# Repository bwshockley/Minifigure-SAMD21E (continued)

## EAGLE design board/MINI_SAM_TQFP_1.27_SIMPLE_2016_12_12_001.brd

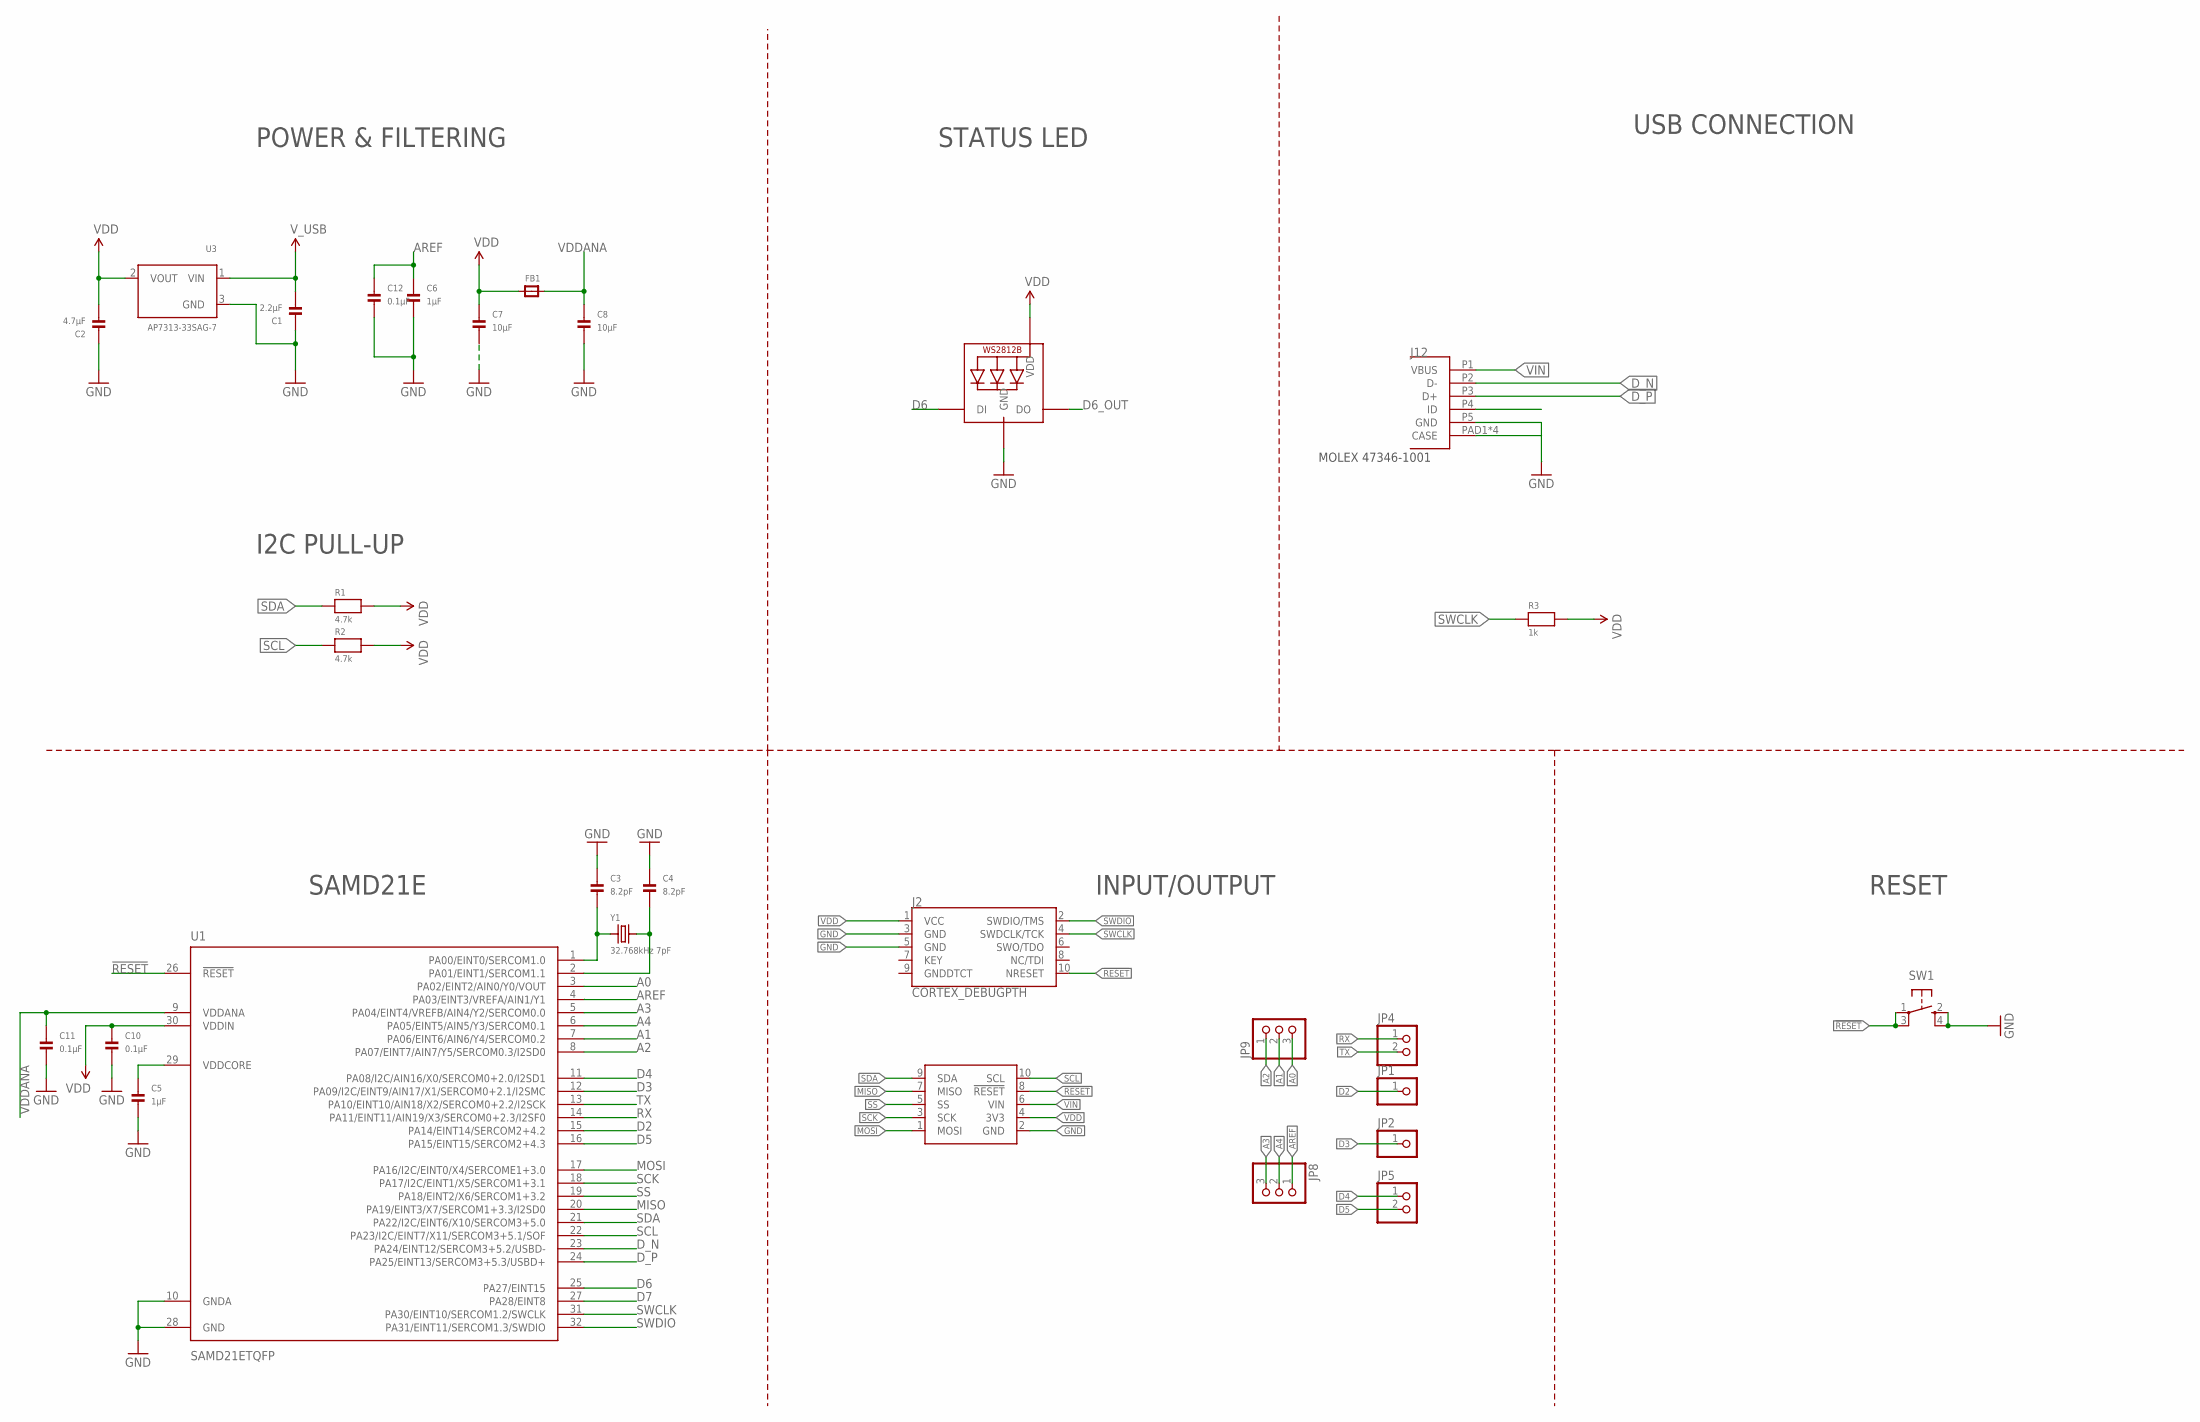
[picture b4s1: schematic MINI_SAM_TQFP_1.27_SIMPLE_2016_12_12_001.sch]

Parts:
C1: 2.2µF; _0805MP
C2: 4.7µF; _0805MP
C3, C4: 8.2pF; _0805MP
C5, C6: 1µF; _0805MP
C7, C8: 10µF; _0805MP
C10, C11, C12: 0.1µF; _0805MP
FB1: FERRITE_0805MP; _0805MP
J2: CORTEX_DEBUGPTH; 2X5-PTH-1.27MM
J12: MOLEX_47346-100147346; MOLEX_47346-1001
JP1, JP2: HEADER-1X1ROUND; 1X01_ROUND
JP4, JP5: HEADER-1X2ROUND; 1X02_ROUND
JP8, JP9: HEADER-1X3ROUND; 1X03_ROUND
R1, R2: 4.7k; _0805MP
R3: 1k; _0805MP
STATUS: WS2812B3535; LED3535
SW1: SPST_TACT-KMR2; KMR2
U1: SAMD21ETQFP; TQFP32-08
U3: AP7313-33SAG-7; SOT23-R
U$3: MINI_SAM_10_PIN; M50-360XXXX
Y1: 32.768kHz 7pF; _0805MP

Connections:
!RESET: J2.10 (NRESET), SW1.1, SW1.3 (P1), U1.26 (!RESET), U$3.8 (!RESET)
A0: JP9.3, U1.3 (PA02/EINT2/AIN0/Y0/VOUT)
A1: JP9.2, U1.7 (PA06/EINT6/AIN6/Y4/SERCOM0.2)
A2: JP9.1, U1.8 (PA07/EINT7/AIN7/Y5/SERCOM0.3/I2SD0)
A3: JP8.3, U1.5 (PA04/EINT4/VREFB/AIN4/Y2/SERCOM0.0)
A4: JP8.2, U1.6 (PA05/EINT5/AIN5/Y3/SERCOM0.1)
AREF: C6.1, C12.1, JP8.1, U1.4 (PA03/EINT3/VREFA/AIN1/Y1)
D2: JP1.1, U1.15 (PA14/EINT14/SERCOM2+4.2)
D3: JP2.1, U1.12 (PA09/I2C/EINT9/AIN17/X1/SERCOM0+2.1/I2S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)
D4: JP5.1, U1.11 (PA08/I2C/AIN16/X0/SERCOM0+2.0/I2SD1)
D5: JP5.2, U1.16 (PA15/EINT15/SERCOM2+4.3)
D6: STATUS.1 (DI), U1.25 (PA27/EINT15)
D6_OUT: STATUS.3 (DO)
D7: U1.27 (PA28/EINT8)
D_N: J12.P2 (D-), U1.23 (PA24/EINT12/SERCOM3+5.2/USBD-)
D_P: J12.P3 (D+), U1.24 (PA25/EINT13/SERCOM3+5.3/USBD+)
GND: C1.1, C2.1, C3.1, C4.1, C5.2, C6.2, C7.2, C8.2, C10.2, C11.2, C12.2, J2.3 (GND), J2.5 (GND), J12.P5 (GND), J12.PAD1 (CASE), J12.PAD2 (CASE), J12.PAD3 (CASE), J12.PAD4 (CASE), STATUS.4 (GND), SW1.2 (S), SW1.4 (S1), U1.10 (GNDA), U1.28 (GND), U3.3 (GND), U$3.2 (GND)
MISO: U1.20 (PA19/EINT3/X7/SERCOM1+3.3/I2SD0), U$3.7 (MISO)
MOSI: U1.17 (PA16/I2C/EINT0/X4/SERCOME1+3.0), U$3.1 (MOSI)
unnamed: C3.2, U1.1 (PA00/EINT0/SERCOM1.0), Y1.1
unnamed: C4.2, U1.2 (PA01/EINT1/SERCOM1.1), Y1.2
unnamed: C5.1, U1.29 (VDDCORE)
RX: JP4.1, U1.14 (PA11/EINT11/AIN19/X3/SERCOM0+2.3/I2SF0)
SCK: U1.18 (PA17/I2C/EINT1/X5/SERCOM1+3.1), U$3.3 (SCK)
SCL: R2.1, U1.22 (PA23/I2C/EINT7/X11/SERCOM3+5.1/SOF), U$3.10 (SCL)
SDA: R1.1, U1.21 (PA22/I2C/EINT6/X10/SERCOM3+5.0), U$3.9 (SDA)
SS: U1.19 (PA18/EINT2/X6/SERCOM1+3.2), U$3.5 (SS)
SWCLK: J2.4 (SWDCLK/TCK), R3.1, U1.31 (PA30/EINT10/SERCOM1.2/SWCLK)
SWDIO: J2.2 (SWDIO/TMS), U1.32 (PA31/EINT11/SERCOM1.3/SWDIO)
TX: JP4.2, U1.13 (PA10/EINT10/AIN18/X2/SERCOM0+2.2/I2SCK)
VDD: C2.2, C7.1, C10.1, FB1.1, J2.1 (VCC), R1.2, R2.2, R3.2, STATUS.2 (VDD), U1.30 (VDDIN), U3.2 (VOUT), U$3.4 (3V3)
VDDANA: C8.1, C11.1, FB1.2, U1.9 (VDDANA)
VIN: C1.2, J12.P1 (VBUS), U3.1 (VIN), U$3.6 (VIN)

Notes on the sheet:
INPUT/OUTPUT
RESET
POWER & FILTERING
SAMD21E
STATUS LED
USB CONNECTION
I2C PULL-UP
MOLEX 47346-1001

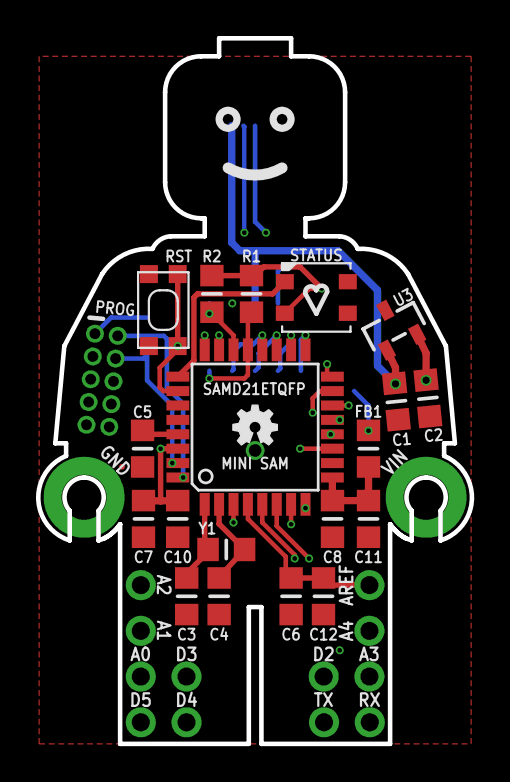
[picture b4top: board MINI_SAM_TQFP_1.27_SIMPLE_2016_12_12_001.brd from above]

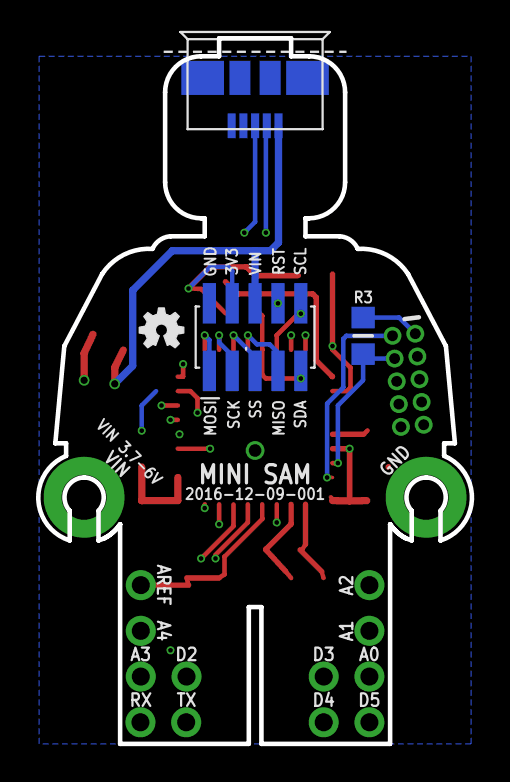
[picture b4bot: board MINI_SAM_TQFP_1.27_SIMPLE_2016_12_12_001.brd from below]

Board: 4 copper layers, 24.1 x 39.2 mm, 31 parts (4 on the bottom side), 31 nets.

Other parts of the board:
U$1, U$2: OSHW-LOGO-MINI

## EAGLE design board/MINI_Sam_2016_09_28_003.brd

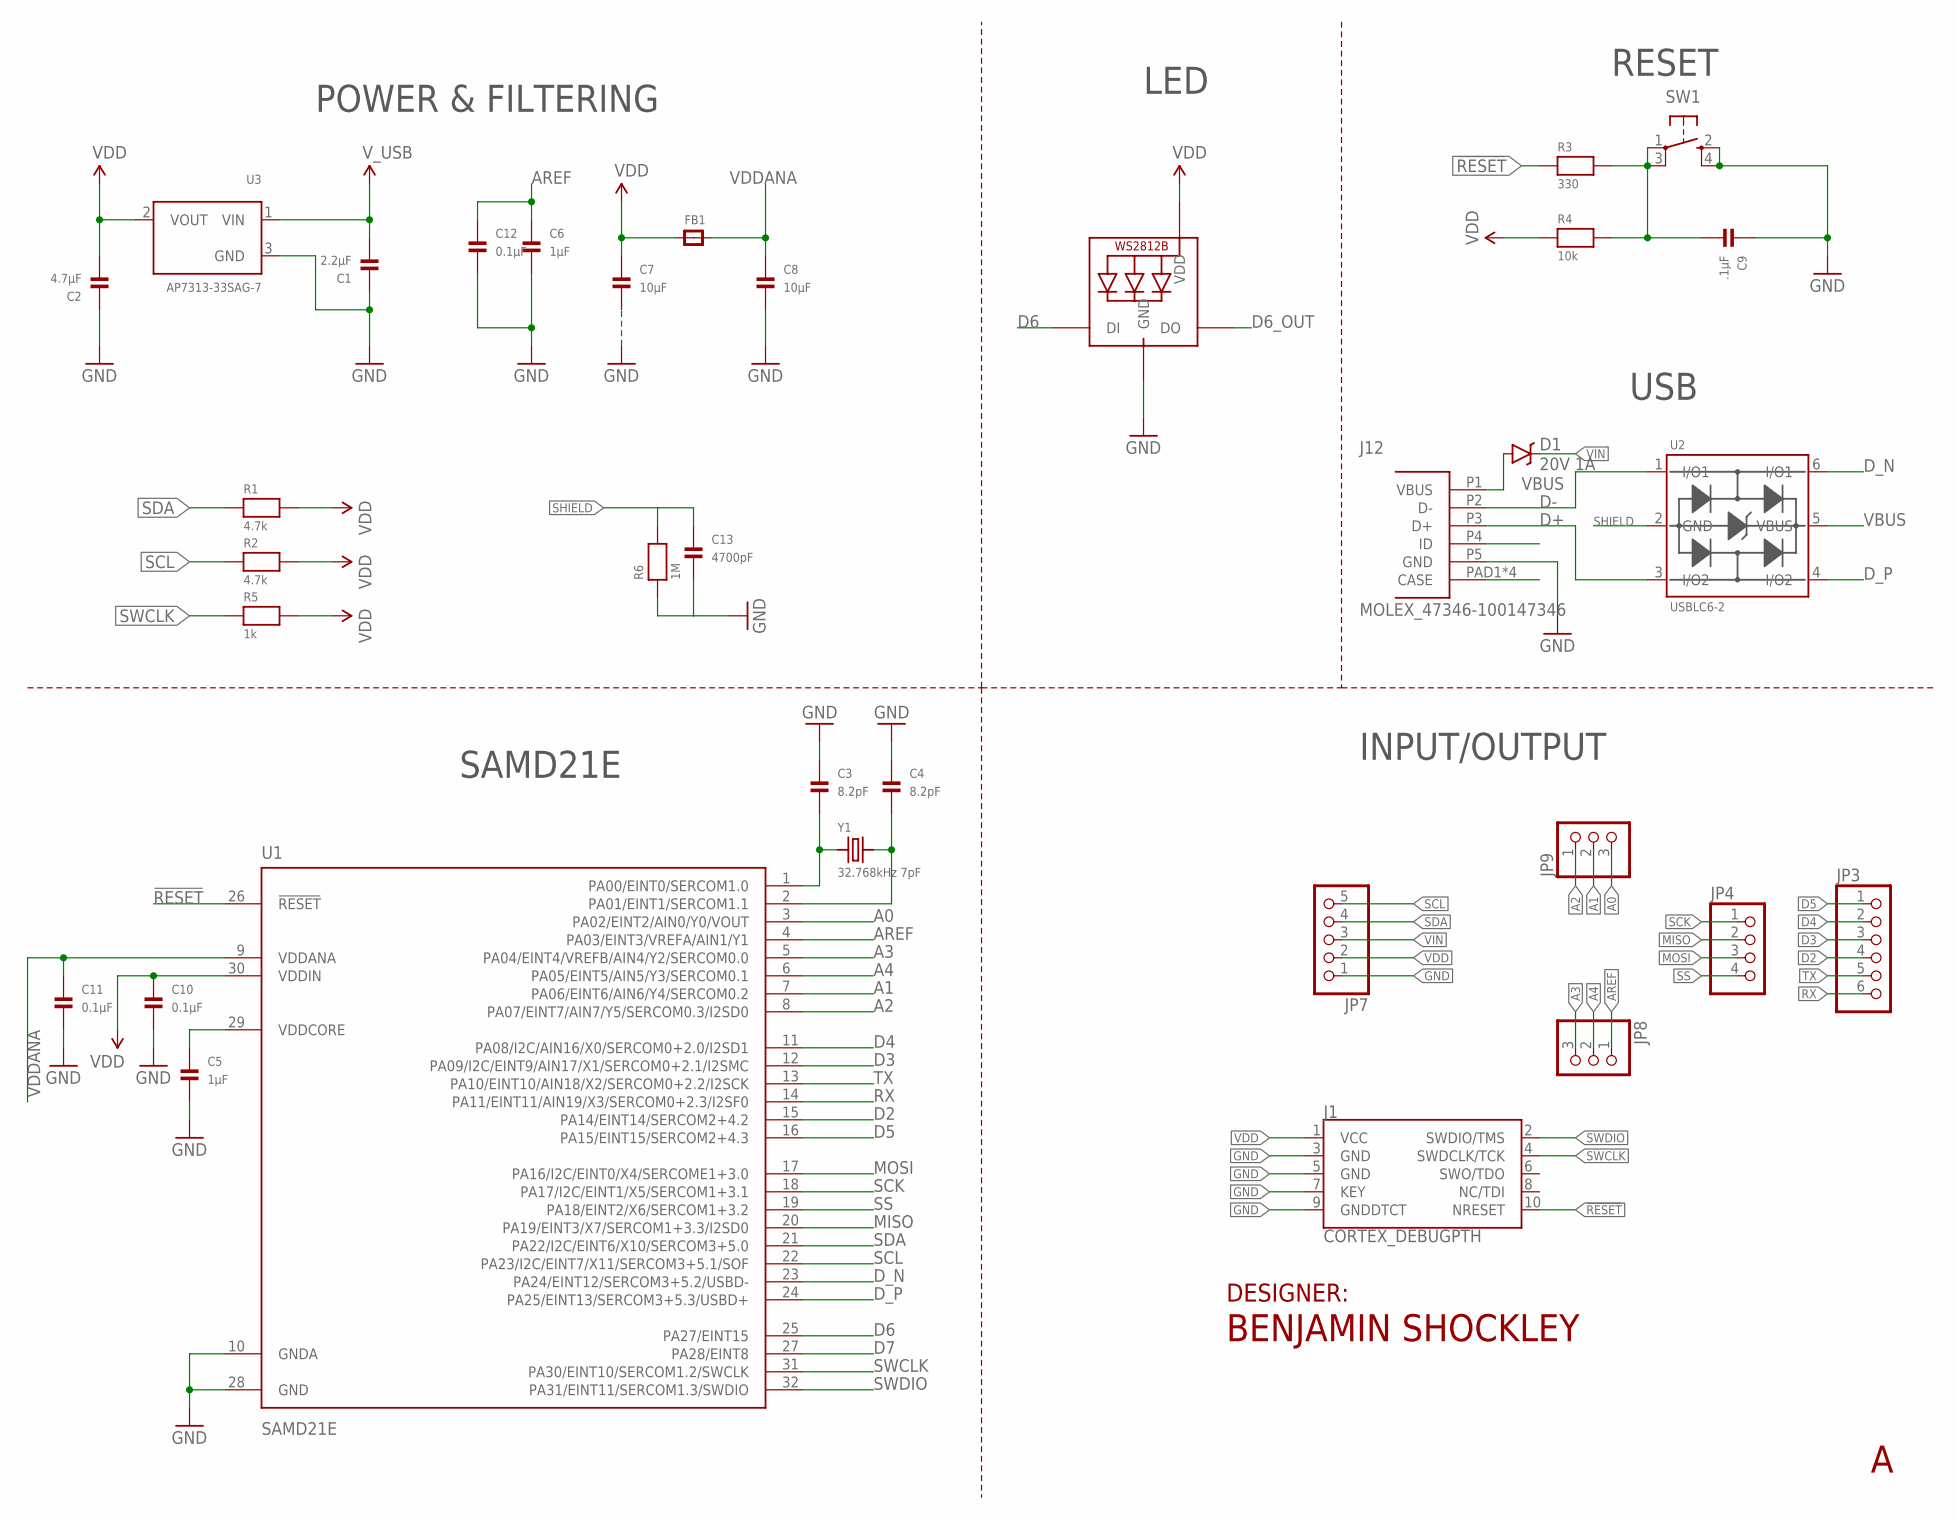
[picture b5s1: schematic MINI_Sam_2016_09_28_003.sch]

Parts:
C1: 2.2µF; _0805MP
C2: 4.7µF; _0805MP
C3, C4: 8.2pF; _0805MP
C5, C6: 1µF; _0805MP
C7, C8: 10µF; _0805MP
C9: .1µF; _0805MP
C10, C11, C12: 0.1µF; _0805MP
C13: 4700pF; _0805MP
D1: 20V 1A; _0805MP
FB1: FERRITE_0805MP; _0805MP
J1: CORTEX_DEBUGPTH; 2X5-PTH-1.27MM
J12: MOLEX_47346-100147346; MOLEX_47346-1001
JP3: HEADER-1X6ROUND; 1X06_ROUND
JP4: HEADER-1X4ROUND; 1X04_ROUND
JP7: HEADER-1X5ROUND; 1X05_ROUND
JP8, JP9: HEADER-1X3ROUND; 1X03_ROUND
LED: WS2812B3535; LED3535
R1, R2: 4.7k; _0805MP
R3: 330; _0805MP
R4: 10k; _0805MP
R5: 1k; _0805MP
R6: 1M; _0805MP
SW1: SPST_TACT-KMR2; KMR2
U1: SAMD21E; QFN32
U2: USBLC6-2; SOT23-6L
U3: AP7313-33SAG-7; SOT23-R
Y1: 32.768kHz 7pF; _0805MP

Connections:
!RESET: J1.10 (NRESET), R3.1, U1.26 (!RESET)
A0: JP9.3, U1.3 (PA02/EINT2/AIN0/Y0/VOUT)
A1: JP9.2, U1.7 (PA06/EINT6/AIN6/Y4/SERCOM0.2)
A2: JP9.1, U1.8 (PA07/EINT7/AIN7/Y5/SERCOM0.3/I2SD0)
A3: JP8.3, U1.5 (PA04/EINT4/VREFB/AIN4/Y2/SERCOM0.0)
A4: JP8.2, U1.6 (PA05/EINT5/AIN5/Y3/SERCOM0.1)
AREF: C6.1, C12.1, JP8.1, U1.4 (PA03/EINT3/VREFA/AIN1/Y1)
D2: JP3.4, U1.15 (PA14/EINT14/SERCOM2+4.2)
D3: JP3.3, U1.12 (PA09/I2C/EINT9/AIN17/X1/SERCOM0+2.1/I2S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)
D4: JP3.2, U1.11 (PA08/I2C/AIN16/X0/SERCOM0+2.0/I2SD1)
D5: JP3.1, U1.16 (PA15/EINT15/SERCOM2+4.3)
D6: LED.1 (DI), U1.25 (PA27/EINT15)
D6_OUT: LED.3 (DO)
D7: U1.27 (PA28/EINT8)
D+: J12.P3 (D+), U2.3 (I/O2)
D-: J12.P2 (D-), U2.1 (I/O1)
D_N: U1.23 (PA24/EINT12/SERCOM3+5.2/USBD-), U2.6 (I/O1)
D_P: U1.24 (PA25/EINT13/SERCOM3+5.3/USBD+), U2.4 (I/O2)
GND: C1.1, C2.1, C3.1, C4.1, C5.2, C6.2, C7.2, C8.2, C9.1, C10.2, C11.2, C12.2, C13.2, J1.3 (GND), J1.5 (GND), J1.7 (KEY), J1.9 (GNDDTCT), J12.P5 (GND), JP7.1, LED.4 (GND), R6.1, SW1.2 (S), SW1.4 (S1), U1.10 (GNDA), U1.28 (GND), U3.3 (GND)
MISO: JP4.2, U1.20 (PA19/EINT3/X7/SERCOM1+3.3/I2SD0)
MOSI: JP4.3, U1.17 (PA16/I2C/EINT0/X4/SERCOME1+3.0)
unnamed: C3.2, U1.1 (PA00/EINT0/SERCOM1.0), Y1.1
unnamed: C9.2, R3.2, R4.2, SW1.1, SW1.3 (P1)
unnamed: C4.2, U1.2 (PA01/EINT1/SERCOM1.1), Y1.2
unnamed: C5.1, U1.29 (VDDCORE)
RX: JP3.6, U1.14 (PA11/EINT11/AIN19/X3/SERCOM0+2.3/I2SF0)
SCK: JP4.1, U1.18 (PA17/I2C/EINT1/X5/SERCOM1+3.1)
SCL: JP7.5, R2.1, U1.22 (PA23/I2C/EINT7/X11/SERCOM3+5.1/SOF)
SDA: JP7.4, R1.1, U1.21 (PA22/I2C/EINT6/X10/SERCOM3+5.0)
SHIELD: C13.1, J12.PAD1 (CASE), J12.PAD2 (CASE), J12.PAD3 (CASE), J12.PAD4 (CASE), R6.2, U2.2 (GND)
SS: JP4.4, U1.19 (PA18/EINT2/X6/SERCOM1+3.2)
SWCLK: J1.4 (SWDCLK/TCK), R5.1, U1.31 (PA30/EINT10/SERCOM1.2/SWCLK)
SWDIO: J1.2 (SWDIO/TMS), U1.32 (PA31/EINT11/SERCOM1.3/SWDIO)
TX: JP3.5, U1.13 (PA10/EINT10/AIN18/X2/SERCOM0+2.2/I2SCK)
VBUS: D1.1 (A), J12.P1 (VBUS), U2.5 (VBUS)
VDD: C2.2, C7.1, C10.1, FB1.1, J1.1 (VCC), JP7.2, LED.2 (VDD), R1.2, R2.2, R4.1, R5.2, U1.30 (VDDIN), U3.2 (VOUT)
VDDANA: C8.1, C11.1, FB1.2, U1.9 (VDDANA)
VIN: C1.2, D1.2 (C), JP7.3, U3.1 (VIN)

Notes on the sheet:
INPUT/OUTPUT
RESET
POWER & FILTERING
SAMD21E
USB
LED
DESIGNER:

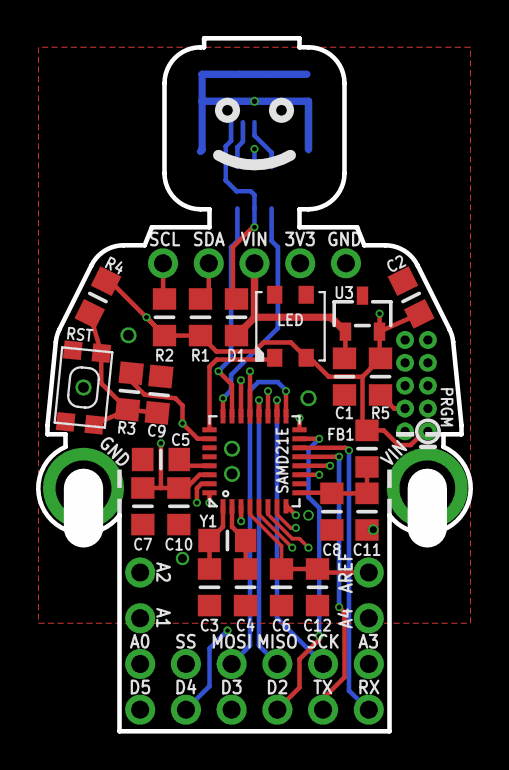
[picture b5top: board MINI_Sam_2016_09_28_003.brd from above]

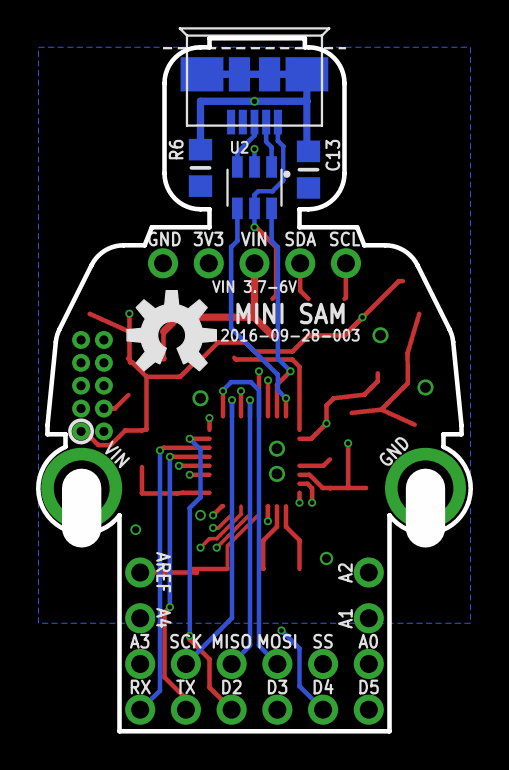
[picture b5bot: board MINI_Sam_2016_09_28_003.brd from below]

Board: 4 copper layers, 24.0 x 38.5 mm, 35 parts (5 on the bottom side), 36 nets.

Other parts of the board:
U$1: OSHW-LOGO-M

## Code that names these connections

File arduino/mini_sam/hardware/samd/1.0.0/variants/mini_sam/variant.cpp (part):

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 *
 * | Arduino Pin Number |    Silkscreen    |  PIN   |   Alt. Function   | Comments (! means unavailable with this variant)
 * +--------------------+------------------+--------+-------------------+-------------------------------------------------
 * | --                 | --               |  PA00  | Xin32             | Xin32
 * | --                 | --               |  PA01  | Xout32            | Xout32
 * | 2                  | A0               |  PA02  |                   | EIC/EXTINT[2] ADC/AIN[0] PTC/Y[0] DAC/VOUT
 * | 3                  | AREF             |  PA03  | REFA              | EIC/EXTINT[3] REF/ADC/VREFA REF/DAC/VREFA ADC/AIN[1] PTC/Y[1]
 * | 4                  | ~A3              |  PA04  |                   | EIC/EXTINT[4] REF/ADC/VREFB ADC/AIN[4] AC/AIN[0] PTC/Y[2] !SERCOM0/PAD[0] TCC0/WO[0]
 * | 5                  | ~A4              |  PA05  |                   | EIC/EXTINT[5] ADC/AIN[5] AC/AIN[1] PTC/Y[3] !SERCOM0/PAD[1] TCC0/WO[1]
 * | 6                  | ~A1              |  PA06  |                   | !EIC/EXTINT[6] ADC/AIN[6] AC/AIN[2] PTC/Y[4] !SERCOM0/PAD[2] TCC1/WO[0]
 * | 7                  | ~A2              |  PA07  | Voltage Divider   | !EIC/EXTINT[7] ADC/AIN[7] AC/AIN[3] PTC/Y[5] !SERCOM0/PAD[3] TCC1/WO[1]
 * | 8                  | ~A5              |  PA08  |                   | EIC/NMI ADC/AIN[16] PTC/X[0] !SERCOM0/PAD[0] !SERCOM2/PAD[0] !TCC0/WO[0] TCC1/WO[2]
 * | 9                  | ~A6              |  PA09  |                   | EIC/EXTINT[9] ADC/AIN[17] PTC/X[1] !SERCOM0/PAD[1] !SERCOM2/PAD[1] !TCC0/WO[1] TCC1/WO[3]
 * | 10                 | TX               |  PA10  | TX                | !EIC/EXTINT[10] ADC/AIN[18] PTC/X[2] SERCOM0/PAD[2] !SERCOM2/PAD[2] !TCC1/WO[0] TCC0/WO[2]
 * | 11                 | RX               |  PA11  | RX                | !EIC/EXTINT[11] ADC/AIN[19] PTC/X[3] SERCOM0/PAD[3] !SERCOM2/PAD[3] !TCC1/WO[1] TCC0/WO[3]
 * | 14                 | ~14              |  PA14  |                   | EIC/EXTINT[14] SERCOM2/PAD[2] !TC3/WO[0] TCC0/WO[4]
 * | 15                 | ~15              |  PA15  | LED               | !EIC/EXTINT[15] SERCOM2/PAD[3] !TC3/WO[1] TCC0/WO[5]
 * | --                 | RST              |  ----  |                   | Reset
 * | --                 | Gnd              |  ----  |                   | Ground
 * | --                 | VDD              |  ----  |                   | VDD 3.3V
 * | --                 | Vin              |  ----  |                   | Vin 3.7V - 6.0V
 * | 16                 | ~MOSI            |  PA16  | SPI MOSI          | EIC/EXTINT[0] PTC/X[4] SERCOM1/PAD[0] !SERCOM3/PAD[0] TCC2/WO[0] !TCC0/WO[6]
 * | 17                 | ~SCK             |  PA17  | SPI SCK           | EIC/EXTINT[1] PTC/X[5] SERCOM1/PAD[1] !SERCOM3/PAD[1] TCC2/WO[1] !TCC0/WO[7]
 * | 18                 | ~SS              |  PA18  | SPI SS            | EIC/EXTINT[2] PTC/X[6] SERCOM1/PAD[2] !SERCOM3/PAD[2] TC3/WO[0] !TCC0/WO[2]
 * | 19                 | ~MISO            |  PA19  | SPI MISO          | EIC/EXTINT[3] PTC/X[7] SERCOM1/PAD[3] !SERCOM3/PAD[3] TC3/WO[1] !TCC0/WO[3]
 * | 22                 | ~SDA             |  PA22  | I2C/SDA w/pullup  | EIC/EXTINT[6] PTC/X[10] SERCOM3/PAD[0] !SERCOM5/PAD[0] TC4/WO[0] !TCC0/WO[4]
 * | 23                 | ~SCL             |  PA23  | I2C/SCL w/pullup  | EIC/EXTINT[7] PTC/X[11] SERCOM3/PAD[1] !SERCOM5/PAD[1] TC4/WO[1] !TCC0/WO[5]
 * | --                 | --               |  PA24  | USB Data -        | USB Connector
 * | --                 | --               |  PA25  | USB Data +        | USB Connector
 * | 27                 | 27               |  PA27  | RGB LED           | EIC/EXTINT[15] WS2812B LED
 * | 28                 | 28               |  PA28  |                   | EIC/EXTINT[15] Button
 * | 30                 | --               |  PA30  | SWD CLK           | EIC/EXTINT[10] !SERCOM1/PAD[2] TCC1/WO[0] SWD CLK
 * | 31                 | --               |  PA31  | SWD IO            | EIC/EXTINT[11] !SERCOM1/PAD[3] TCC1/WO[1] SWD IO
 * +--------------------+------------------+--------+-------------------+-------------------------------------------------
 *
 * You may use Arduino pin numbers ranging from 0 to 31.
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
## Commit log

2016-10-06 Added PDF of Schematic
2016-10-06 Updated README.md
    Filled in some details.
2016-10-06 Add SCH and BRD Files
    Initial Files added.
2016-10-25 New Boards
    Added new boards with a better defined boarder, and added a 2mm pitch, 2x6 SMD header option for USB/Programming/SDA/SPI.
2016-10-25 Added MINI SAM #2 Schematic
    PDF of schematic for MINI SAM with 2mm header.
2016-10-25 Update for Board Links
    Added links to shared projects on OSHPark.
2016-12-09 Uploaded TQFP SIMPLE
    MINI SAM with TQFP SAMD21E and removed unnecessary USB protection and reset debounce.
2016-12-09 Uploaded TQFP SIMPLE SCHEMATIC
2016-12-09 Updated for TQFP SIMPLE
2016-12-12 Add 1.27mm Pitch SIMPLE
2016-12-12 Added 1.27mm Pitch SIMPLE
2017-01-16 Added 2.54_BB Version
2017-01-20 Create README.md
    Placeholder README while I prepare files.
2017-01-24 Create license.md
    Added CC BY SA License File
2017-01-26 Create README.md
    Initial Creation - added board via upload.
2017-01-26 Add files via upload
    Added the PDF schematic.
2017-01-26 Update README.md
    Added clarity and fixed a couple PIN assignment mistakes.
2017-01-27 Updated bootloader file
    Pointed the bootloader to the latest build for Mini SAM.
2017-01-27 Update VARIANT_COMPLIANCE_CHANGELOG
2017-01-27 Cleanup and PIN 28 Change
    Formatting clean up and reference to PIN28 cleaned up.
2017-01-27 Fixed LED_PIN
    Fixed LED_PIN to reference PIN 15 instead of PIN 14.
2017-01-27 Fixed LED PIN
    Fixed reference to LED PIN from 14 to 15.
2017-01-27 Updated Internal Layer
    Updated one of the internal layers to include a ground plane for better grounding.
2017-01-27 Update to -002
    Name change to reflect latest files.
2017-01-27 Updated to -002
2017-02-03 Create minifigure.lbr
    Created the basic minifigure library. Add this library to your Eagle libraries to add a LEGO minifigure sized board outline with two vias for hands.
2017-02-03 Added -010 Version
    Minor Changes to BOM - Voltage Regulator and USB Protection. Added a couple minor aesthetic changes as well. 1980's Space Man!
2017-02-04 BOM for Oct 6th Minifigure-SAMD21E On OSHPARK
    BOM for Oct 6th Minifigure-SAMD21E On OSHPARK
2017-02-16 Added Builtin_Button removed Extra SERCOM
    Added definition for the built in Button attached to PIN 28 to be accessible via "BUTTON_BUILTIN".
    Removed SERCOM4 and SERCOM5 definitions as the SAMD21E does not have these SERCOMs.
2017-02-16 Removed SERCOM4&5, Updated PORTA3
2017-02-20 Added V12 to 2017-01
    Added V12 with minor cosmetic changes.
2017-02-20 Added V12 Details
    V12 is the same as V10 with minor cosmetic changes.
2017-02-24 Update to I2C Jumper
    Fixed the I2C disconnect jumper.
2018-10-22 Added v2.0.0
2018-10-22 Remove SERCOM 4 & 5
2018-10-22 Removed SERCOM - Cleanup
    General cleanup.
